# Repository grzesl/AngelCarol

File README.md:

# AngelCarol
AngelCarol is project that contains necessary information to build Angel statue that sings carols.

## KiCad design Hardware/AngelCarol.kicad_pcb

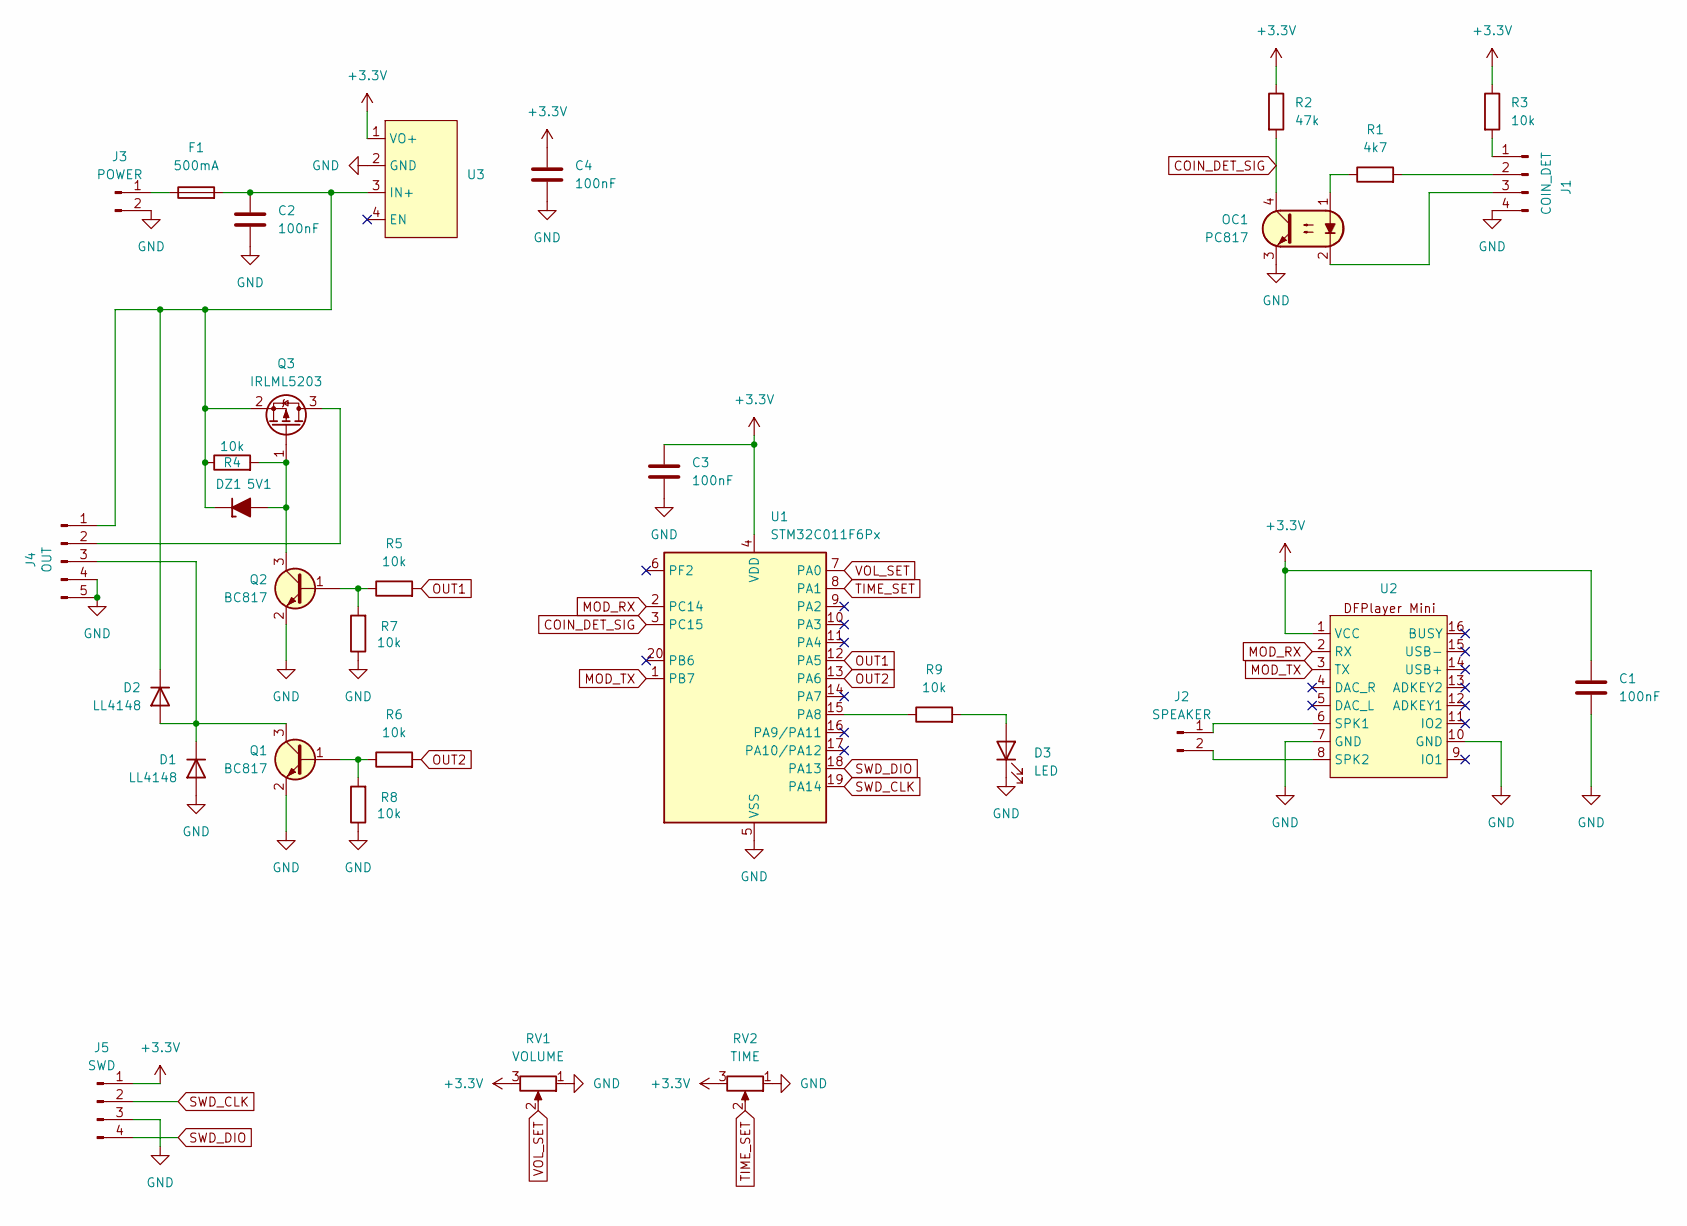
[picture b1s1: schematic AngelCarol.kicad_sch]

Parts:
C1, C2, C3, C4: 100nF; C_0805_2012Metric
D1, D2: LL4148; D_MiniMELF
D3: LED; LED_D3.0mm
DZ1: 5V1; D_T-1_P5.08mm_Horizontal
F1: 500mA; Fuse_1206_3216Metric_Pad1.42x1.75mm_HandSolder
J1: COIN_DET; PinHeader_1x04_P2.54mm_Vertical
J2: SPEAKER; PinHeader_1x02_P2.54mm_Vertical
J3: POWER; PinHeader_1x02_P2.54mm_Vertical
J4: OUT; PinHeader_1x05_P2.54mm_Vertical
J5: SWD; PinHeader_1x04_P2.54mm_Vertical
OC1: PC817; DIP-4_W7.62mm
Q1, Q2: BC817; SOT-23
Q3: IRLML5203; SOT-23
R1: 4k7; R_0805_2012Metric
R2: 47k; R_0805_2012Metric
R3, R4, R5, R6, R7, R8, R9: 10k; R_0805_2012Metric
RV1: VOLUME; POT_BLUE
RV2: TIME; POT_BLUE
U1: STM32C011F6Px; TSSOP-20_4.4x6.5mm_P0.65mm
U2: DFPlayerMini
U3: DCDC_PRESET

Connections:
+3.3V: C1.1, C3.1, C4.1, J5.1, R2.1, R3.1, RV1.3, RV2.3, U1.4 (VDD), U2.1 (VCC), U3.1 (VO+)
COIN_DET_SIG: OC1.4, R2.2, U1.3 (PC15)
GND: C1.2, C2.2, C3.2, C4.2, D1.2 (A), D3.1 (K), J1.4, J3.2, J4.4, J4.5, J5.3, OC1.3, Q1.2 (E), Q2.2 (E), R7.1, R8.1, RV1.1, RV2.1, U1.5 (VSS), U2.7 (GND), U2.10 (GND), U3.2 (GND)
MOD_RX: U1.2 (PC14), U2.2 (RX)
MOD_TX: U1.1 (PB7), U2.3 (TX)
unnamed: D1.1 (K), D2.2 (A), J4.3, Q1.3 (C)
unnamed: C2.1, D2.1 (K), DZ1.1 (K), F1.2, J4.1, Q3.2 (S), R4.1, U3.3 (IN+)
unnamed: D3.2 (A), R9.2
unnamed: DZ1.2 (A), Q2.3 (C), Q3.1 (G), R4.2
unnamed: J1.1, R3.2
unnamed: J1.2, R1.2
unnamed: J1.3, OC1.2
unnamed: J2.1, U2.6 (SPK1)
unnamed: J2.2, U2.8 (SPK2)
unnamed: F1.1, J3.1
unnamed: J4.2, Q3.3 (D)
unnamed: OC1.1, R1.1
unnamed: Q1.1 (B), R6.1, R8.2
unnamed: Q2.1 (B), R5.1, R7.2
unnamed: R9.1, U1.15 (PA8)
OUT1: R5.2, U1.12 (PA5)
OUT2: R6.2, U1.13 (PA6)
SWD_CLK: J5.2, U1.19 (PA14)
SWD_DIO: J5.4, U1.18 (PA13)
TIME_SET: RV2.2, U1.8 (PA1)
VOL_SET: RV1.2, U1.7 (PA0)

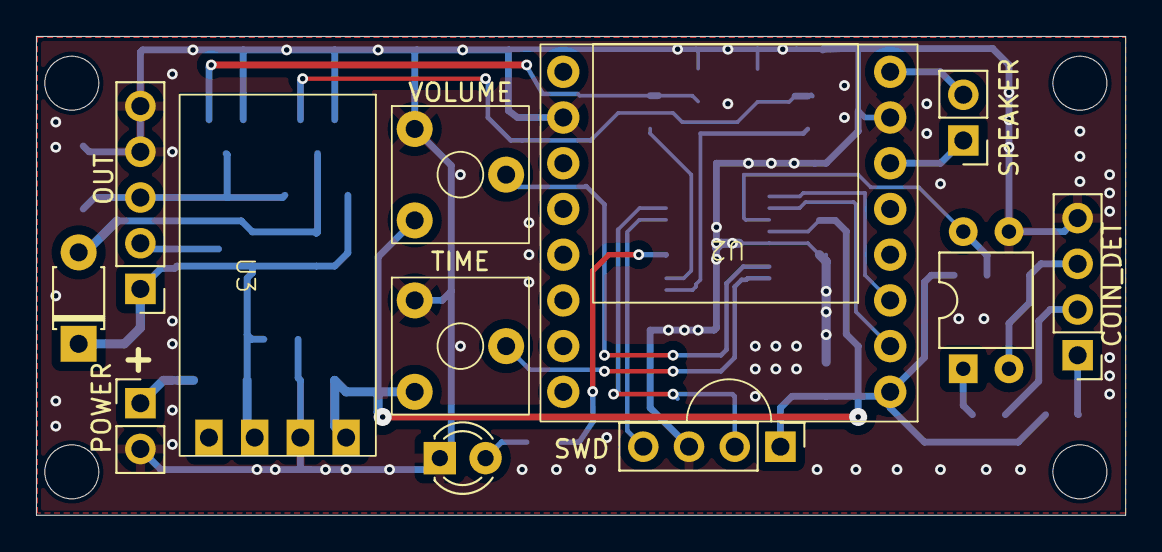
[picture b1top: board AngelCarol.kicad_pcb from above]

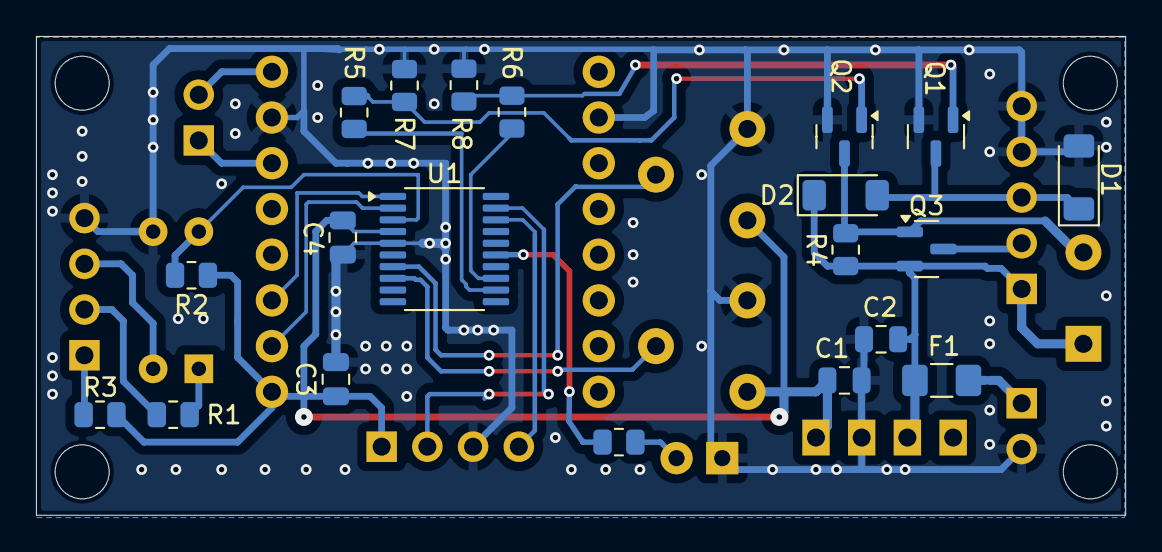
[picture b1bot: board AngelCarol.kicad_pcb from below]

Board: 2 copper layers, 60.5 x 26.6 mm, 32 parts (20 on the bottom side), 26 nets.

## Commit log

2024-11-05 First version on PCB
2024-11-14 Soft initial commit
2024-11-17 List & Events FadeIn & FadeOut
2024-11-18 Few adjustments
2024-11-22 gitignore correction
2024-11-30 Tune some components values, add PK handler model
2024-11-30 Add Sloeber project
2024-11-30 Sloeber project changes
2024-12-02 Add Cover 3D model
2024-12-02 Add file with global board definition
2024-12-02 Some fix in schematic
2024-12-02 New main for test version
2024-12-02 Add FreeCAD backups to gitignore
2024-12-03 Relay off aprox 10 sec after carol
2024-12-03 Little change
2024-12-04 gitignore modification
2024-12-05 Modify sufle and setting volume
2024-12-05 Add watchdog
2024-12-07 Use different function to play
